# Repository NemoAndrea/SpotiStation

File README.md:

# SpotiStation - an accessible music player
A **Raspberry Pi** powered **Spotify** music player that aims to be **easy to use for people with cognitive or physical disabilities (e.g. Alzheimer's or MS)**, and allow them to enjoy music independently. 

To suit this purpose, the music player has an **extremely simple interface & operation**. A big play/pause button, a physical linear volume slider, and two side buttons that handle convenience functions, but can be omitted.

While accessibility is the primary aim of the design, this does not mean it cannot be used by a broader audience. If you like the idea of seeing the album art of your Spotify songs, and the physicality of hardware buttons, it would not look out of place in a living room. 

Features

* RGB led matrix that displays cover art and serves as basic visual interface
* Night mode that turns off the display and stops playback at user-set interval
* Lock mode, for caretakers to stop playback for a day
* Audio playback via Bluetooth simplifies wiring and mounting
* Only one plug (power supply)
* Configurable playlist selection, only use a subset of your Spotify playlist for playback
* Playback controllable via Spotify API (e.g. via phone or computer)
* Total parts cost €163 (**excluding printed parts**).
* 3D printed enclosure, making modification easy
* Open python code, low barrier to modification

> **Note** SpotiStation does **not** have any built-in speakers, it needs external bluetooth speakers.

> **Note** SpotiStation is a **standalone** Spotify player and does **not** require a computer or mobile device to run or handle any aspect of playback, although these devices integrate well with the device thanks to the Spotify multi-device API.

### 📖 Manual

A usage manual explaining features and going into details about how features are implemented can be found [on the project wiki](https://github.com/NemoAndrea/SpotiStation/wiki).

### 🔨 Assembly

The assembly of the music player will require some dexterity, screwdrivers, and soldering setup and know-how. If you don't have a soldering setup, you could ask a friend or look for a [maker space](https://en.wikipedia.org/wiki/Hackerspace) that will have the right gear.

A [step-by-step walkthrough of assembly](docs/assembly.md) is available. 

> Feedback on what parts of the assembly are not explained well or are particularly complicated is greatly appreciated. Overly complicated steps could be fixed in future design revisions.

If you find yourself in a situation where accessing the SpotiStation is often difficult and moving the player is not an option, you could consider sourcing the parts for and printing a wireless remote 🎮 for the system. Total parts cost (excluding printed parts) is only around 10 euros, so it is cheap to add. Check out the separate instructions for [the simple wireless remote](docs/assembly-optional-remote.md).

### 💻 Software Setup

The software setup is streamlined as much as possible, but there are some unavoidable difficult steps due to the need to fetch API keys and such for Spotify. If you know how to SSH into your Raspberry Pi, you should be good to go.

The [full step-by-step walkthrough](docs/setup.md) should let you get your own player up and running in no time! 

### 🤔 Alternative solutions

There are other simple music player that focus on accessibility for people with physical or cognitive disabilities. I suggest you check them out and see if they may be better suited for your needs. They are not open source or easily modifiable, but require minimal setup. 

* [the bbrain player](https://bbrain.eu/bbrain-muziekspeler/) - super simple operation, radio and MP3, nice administrator features (hide buttons)
* [The lift Player by smpl](https://smpltec.com/liftplayer-buy-now-us) - super simple operation, plays MP3 files, some administrator features (lock volume)
* [the relish radio player](https://relish-life.com/us/music/radios/relish-radio) - primarily a radio, but can playback MP3 from USB stick
* [the simple music player by iGuerburn](https://www.iguerburn.com/products/dementia-music-player) - plays MP3 files

And because open projects are cool, I will list some other open source projects below

* [dqmusicbox by Ross Porter](https://dqmusicbox.com/) - simple operation, plays MP3 files

### 🙏 Acknowledgements

The programmatically generated text in the UI uses the [silkscreen font by Jason Kottke](https://kottke.org/plus/type/silkscreen/). It is converted to a PIL font for display purposes.

This project is building on similar projects that use the RGB matrix to show album Art. A non-exhaustive list:

* The [spotipi project](https://github.com/ryanwa18/spotipi)  by Ryan Ward
* The [thirtytwopixels project](https://github.com/fspoettel/thirtytwopixels) by Felix Spöttel 

This project was significantly improved by insights gained during the [Delft Open Hardware Academy](https://www.openhardware.academy/01_Welcome.html).

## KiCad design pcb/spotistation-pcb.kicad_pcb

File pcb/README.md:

## SpotiStation shim PCB

This a simple PCB that minimises the spaghetti inside the SpotiStation enclosure. It should be fairly cheap to have it manufactured (less than 6 euros at [Aisler](https://aisler.net/)) with the most basic options.

### Edge.cuts

Board outline is specified in `edge-cuts.dxf` which is generated from the FreeCAD file `edge-cuts.FCStd` file using the 'new' dxf export.

To import it (or modified versions) to kicad, do the following:

1. Open PCB editor
2. File > Import > Graphics
3. Select the `edge-cuts.dxf` file 
4. Placement: at X=`150.82` Y=`106.32`. Make sure to import to the edge.cuts layer and keep the scale to 1. Line width can be chosen at random; 0.1mm is fine.

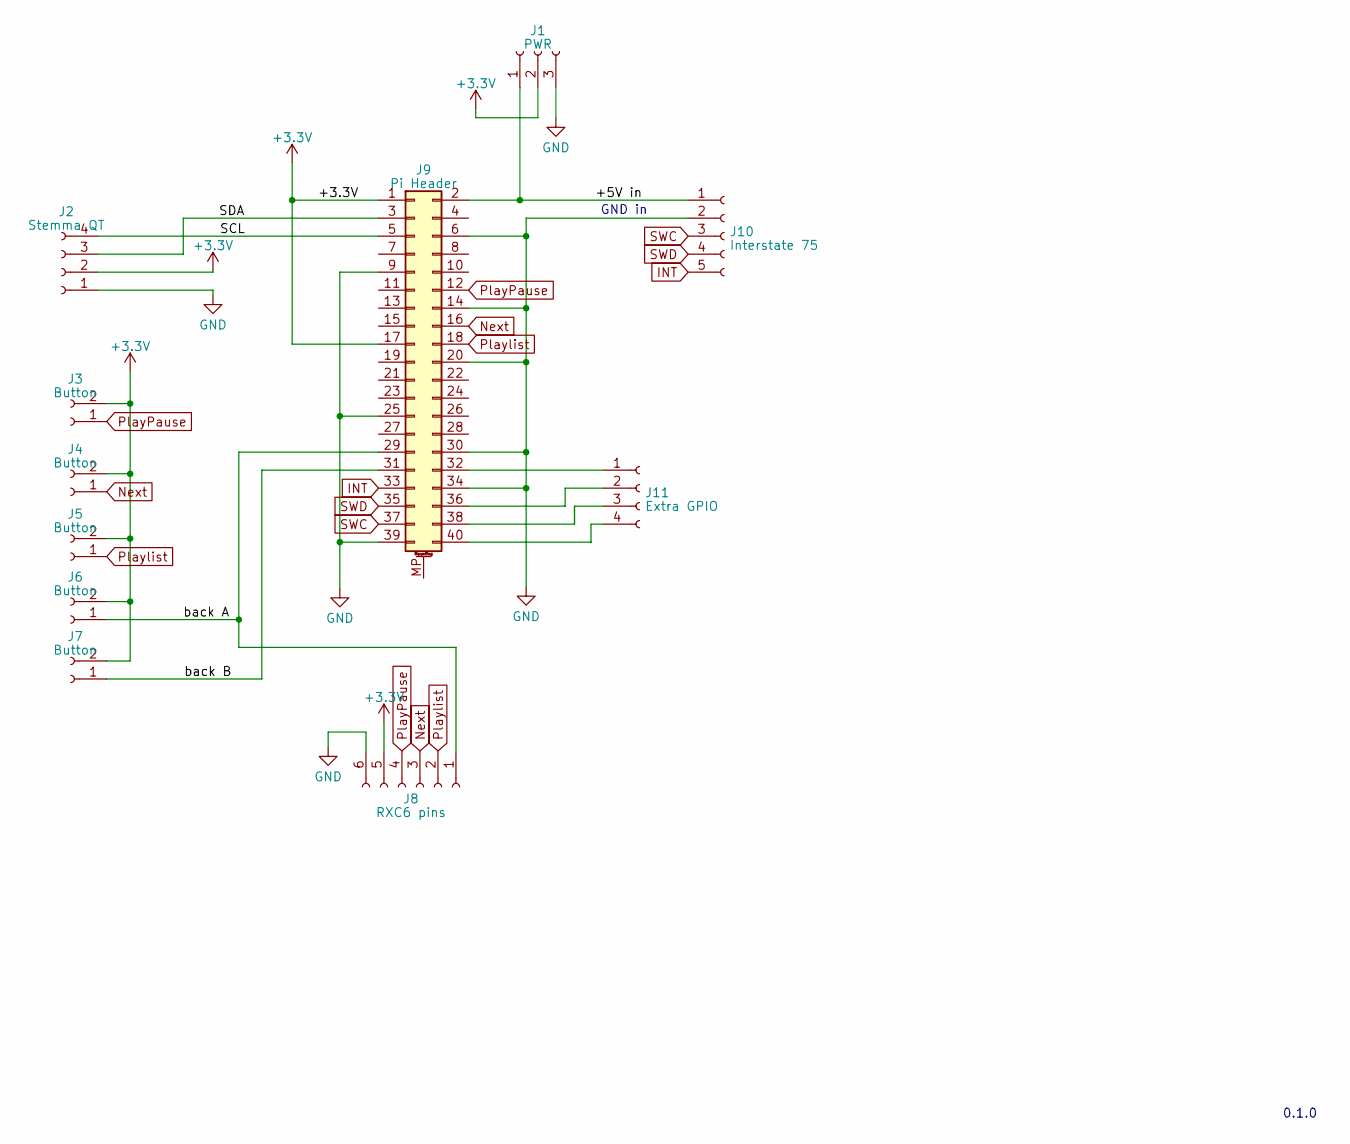
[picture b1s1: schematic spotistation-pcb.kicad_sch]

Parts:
J1: PWR; PinHeader_1x03_P2.54mm_Horizontal
J2: Stemma QT; PinHeader_1x04_P2.54mm_Horizontal
J3, J4, J5, J6, J7: Button; PinHeader_1x02_P2.54mm_Horizontal
J8: RXC6 pins; PinHeader_1x06_P2.54mm_Horizontal
J9: Pi Header; PinSocket_2x20_P2.54mm_Vertical
J10: Interstate 75; PinHeader_1x05_P2.54mm_Horizontal
J11: Extra GPIO; PinHeader_1x04_P2.54mm_Horizontal

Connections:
+3.3V: J1.2, J2.2, J3.2, J4.2, J5.2, J6.2, J7.2, J8.5, J9.1, J9.17
/+5V in: J1.1, J9.2, J10.1
/SCL: J2.4, J9.5
/SDA: J2.3, J9.3
/back A: J6.1, J8.1, J9.29
/back B: J7.1, J9.31
GND: J1.3, J2.1, J8.6, J9.6, J9.9, J9.14, J9.20, J9.25, J9.30, J9.34, J9.39, J10.2
INT: J9.33, J10.5
unnamed: J9.32, J11.1
unnamed: J9.36, J11.2
unnamed: J9.38, J11.3
unnamed: J9.40, J11.4
Next: J4.1, J8.3, J9.16
PlayPause: J3.1, J8.4, J9.12
Playlist: J5.1, J8.2, J9.18
SWC: J9.37, J10.3
SWD: J9.35, J10.4

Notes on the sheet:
GND in
0.1.0

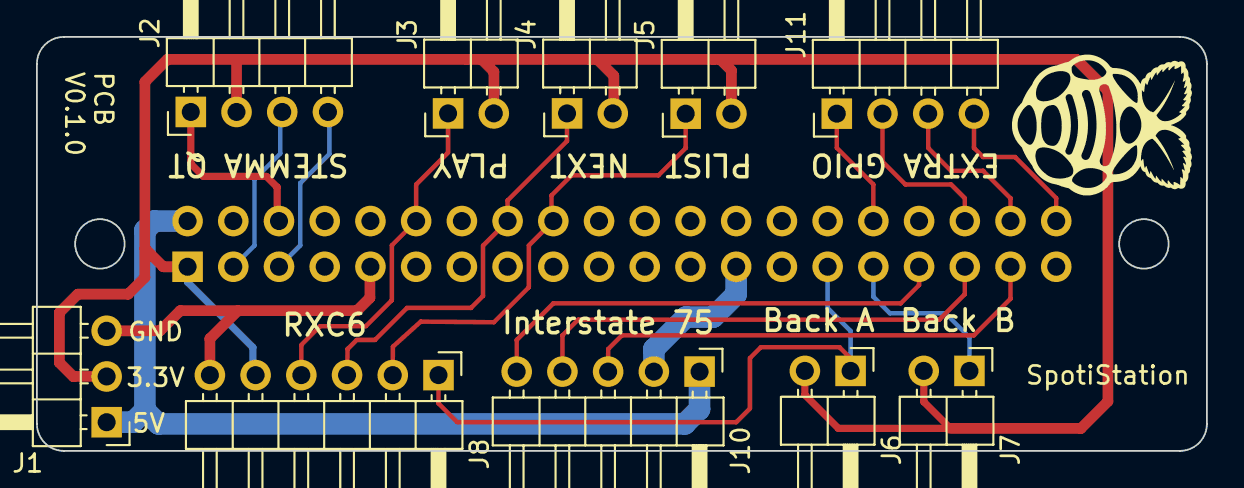
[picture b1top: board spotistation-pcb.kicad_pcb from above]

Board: 2 copper layers, 65.0 x 23.0 mm, 11 parts (1 on the bottom side), 17 nets.

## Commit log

2022-06-19 initial hardware test code
2022-07-09 Intial spotify and bluetooth setup & i2c fix
    Initial instructions on runnable spotify and bluetooth. Also figured out source of issues with neoslider and i2c and found a fix.
2022-07-16 Functional Spotifyd and Spotopy setup
    Functional version of spotifyd (spotify daemon process) and spotipy (python spotify api control). Some refactoring.
2022-07-17 Working display and playpause/skip track
    Display now fetches cover art correctly upon playback and playpause and skip track buttons work. Added remaining hardware checks.
2022-07-17 Basic volume control with slider
    Using pyalsaaudio the slider now adjusts volume. Seems to cause some delay, so perhaps it should be moved to a separate subprocess call to make the loop smoother but it seems functional enough.
2022-07-17 Basic overlay implementation
    Added play/pause and next track overlay and a splash screen
2022-07-17 Update readme
    Trying to add logo
2022-07-18 Add intial 3D printable files
    Basic STL files, needing only minor revisions and possible cleanup of source .blend file
2022-07-23 Basic font drawing capabilities
    Implemented some helper functions using the PIL Textdraw function. Added a countdown to enter boot menu and IP display screen.
2022-07-24 Add playlist.ini to version control
    Adding this file so the basic format is easy to inspect from git
2022-07-24 Setup playlist section
    Add the framework for playlist selection. Still needs a GUI menu to easily select playlists rather than ssh and messing around in a text file.
2022-08-01 Smaller font kerning
    Draw the silkscreen font with 1px kerning to allow more text to be shown on screen at a given moment
2022-08-01 Reorganising of classes
    Move from separate button objects to a convenience class MusicPlayer which makes function call syntax cleaner
2022-08-01 Boot menu update and playlist selection GUI
    Added a proper expandable boot menu and a simple interface to toggle which playlists should be in-rotation and which ones should be ignored. Still need to add the playlist rotation feature to the pla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
2022-08-02 Fix multi-line display issue
    Fix bad performance and display blinking by repeated overlay draws. Now requires explicit overlay-to-image call to add the overlay to the image, to be called when you are done drawing an overlay fram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
2022-08-02 Implemented playlist switching
    Added ability to switch between playlists. Added new flag that forces a local playlist to be chosen. Some documentation improvements.
2022-08-02 Fix: force local playlist flag wasn't implemented correctly
    Now it will do nothing if the current song is part of the in-rotation section, rather than defaulting to picking a random song from the set.
2022-08-02 Added wifi and bluetooth checks
    Simple checks when booting to see if wifi (internet) connection is available and if the device is paired to a bluetooth speaker.
2022-08-02 Fix ip adress display and reorganise files
    Fixed issue with ip adress still using old add_text_overlay instead of the new add_text_to_overlay function syntax. Reorganised interface files under ./media.
2022-08-02 Move configuration to separate ini file
    Moved some of the general configuration files to separate player.ini file.
2022-08-02 Fix typo in config
2022-08-02 Fix: push the correct file
2022-08-02 Improved errors and reliability and setup as service
    Added instructions and tests for running a service on startip.
2022-08-07 Initial work on QUIET and LOCKED states
    Implement some of the logic for the QUIET (night mode) and LOCKED (mute player for the day if someone is getting annoyed by it) states.
2022-08-21 Functional QUIET and LOCKED mode
    Added functionality and interface to QUIET (night) and LOCKED mode. Needs more work on saving some energy in QUIET mode but it's functional
2022-08-27 Implement energy saving night mode
    In QUIET mode display will turn off 30 minutes after the onset of QUIET mode. Pressing any button will temporarily wake the screen to show the QUIET mode panel.
2022-08-27 Add timed overlay song name
    Added a timed overlay showing song name. Uses a gradient backdrop to make song name legible and trims song name to fit on screen.
2022-08-27 Show playlist name when switching between playlists
    Simple text overlay now also shows the playlist name.
2022-08-27 Major docs refactoring
    Moved setup to separate documents and improved the main README to be a better project homepage.
2022-08-29 Add commercial alternatives
    Add links to commercial alternatives to project.
2022-08-29 Docs update with rebrand
    Change some of the documentation to reflect the new repository and project name.
2022-08-29 Part 1 of assembly documentation
    Added list of materials and costs and some instructions on 3D printed. Also added some missing STL (still need to go over their orienation and scale)
2022-08-31 Full assembly documentation
    Finished the assembly documentation.
2022-09-01 Add wiki as submodule
    Add the project wiki containing the manual as a submodule so the two are more closely linked (personal preference).
2022-09-13 Add Raspberry Pi Zero 2 option
    Added Raspberry Pi zero 2 as an option to save on assembly costs. Added alternative stl for RPI zero 2. Updated bill of materials to reflect lowered cost.
2022-09-14 Fix quiet and lock mode config not being respected
    The master boolean for quiet and lock mode was being ignored. Now read it using configparser getboolean() function to parse yes/no (etc)
2022-09-14 Add bootmenu manual QR code
    Add a bootmenu option to show a QR code linking to the github wiki for the project, which serves as a manual.
2022-09-14 Fix QUIET mode display issue
    Fixed issue where the temporary display wake in QUIET mode was not working. This was related to the timer being reset when a new image is drawn. Also fixed issue where the display energy saving mode 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
2022-09-15 Update readme with wiki link
    Add wiki link, clean up typo, remove some of the WIP warnings
2022-09-18 Add logging
    Add initial version of logging. Current error logging and handling is still a bit rough around the edges, but with the current logging system errors can be caught and then handled properly in future 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
2022-09-18 Show song name on pause screen
    Show the name of the currently playing song on the pause overlay.
2022-09-18 Add option to keep song name on screen
    Add option to prevent the song name from automatically fading on screen.
2022-09-18 Update printable files and docs for display diffuser
    Tested and updated changes to the display brackets. Now made to fit 161x168mm cut acrylic panel. Documentation updated to reflect changes.
2022-09-22 Add okh manifest
2022-09-24 Add new banner image
    Add a new banner image that shows the project at a glance. Also added xray view of player - need to check if link works.
2022-09-24 Fix video
    Replace mp4 by gif.
2022-09-24 Fix video
    Also fix video reference in main README
2022-09-24 Update README.md
    Add some important notes for users comparing solutions.
2022-09-28 Update LICENSE
    split licences by aspect of project
2022-10-02 Fix systemd config
    Fix the configuration of the systemd to actually properly auto-restart the player upon error.
2022-10-02 Implement quick and dirty fix for playback timeout
    Implement a solution for playback timeout that will work for now, but needs a more proper solution in the future.
2022-10-02 Update spotify display name and documentation
    Move away from legacy ''msuci_pi'' name and towards the new "SpotiStation" name in spotify. Update the documentation accordingly and expanded a section with more details.
2022-10-16 Implement fix for rare spotifyd error
    Implement a fix for rare case where spotifyd.service is running, but not working correctly. Not sure if fix will always solve issue, but it should improve device reliability.
2022-11-06 More robust timeout handling
    Better solution for handling playback timeout. Still not 100% robust, but much better than the outgoing patch.
2022-11-06 Fix: dangling references to old system
    Some incorrect varaibles were still referenced. Now seems to run without issues again.
2022-12-04 Change to parts list: power supply
    Based on recent tests discussed in https://github.com/NemoAndrea/SpotiStation/issues/9 I have switched out the suggested power supply for a lower power variant which reduces cost and probably increas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
2022-12-11 Update setup.md
    fix error in raspi i2C config
2022-12-11 Update setup.md
    Add important note to use the 32-bit version of OS
2022-12-11 Update setup.md
    Add warning about incomplete documentation
2022-12-11 Fix error logging call
    Error in key function that handles API calls and timeout.
2022-12-11 Update setup.md
    Add better instructions for RGB matrix config
2022-12-12 Fix issue with api timeout when paused for long periods of time
    Implented a fix for API call timeouts when the player has been left paused for a long time and 'currently playing' becomes None according to the API.
2022-12-19 Update setup.md with repo cloning information
    Added information about how to clone the repository onto the raspberry pi. Fixed some outdated image and added preview image for spotify interface.
2022-12-20 Update hardware assembly instructions
    Instructions were missing critical soldering step for display bonnet (solder backside pad E -> 8) which would cause stange issues with display driving.
2023-01-08 Add shuffle option
    Add option to shuffle all playlists via the main config file. In the future a button to toggle shuffle might be added. (e.g. longpress next track)
2023-01-14 New PlayPause button mechanism
    Revised the design for the main play/pause button to be much more robust and have less binding. Return force is still a problem, but at least the part will no longer break under repeated use. Part of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
2023-01-29 Update assembly documentation
    Correct error in images, expanded grounding instructions and show the correct updated playpause button mount part.
2023-01-29 Fix small typo
2023-05-12 Move design files over to FreeCAD
    Redid the design in FreeCAD instead of blender. There are extremely minor differences between the versions. Replaced the STLs with the ones matching the freeCAD design.
2023-08-06 Run volume control as separate service
    Move the volume slider and system volume as a separate script and service to ensure it remains active if the main script crashes. Improved system mute functionality to use system-level muting.
2023-08-12 Basic bluetooth config in boot menu
    Added a basic configuration option in the boot menu to skip the bluetooth connection. Reordered some of the checks in the boot sequence
2023-08-13 Add basic shim PCB
2023-08-20 Add wireless remote build
    Add instructions and files for a simple 433 MHz remote to control the basic functionality of SpotiStation
2024-09-14 Implement documentation update for Spotify API changes
    Add new instructions that reflect the fix for https://github.com/NemoAndrea/SpotiStation/issues/12
